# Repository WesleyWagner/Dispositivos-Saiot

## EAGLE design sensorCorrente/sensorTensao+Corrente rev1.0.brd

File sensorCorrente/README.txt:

sensorTensao+Corrente

Para usar o TC:
-Colocar todos os componentes com prefixo "C.*";
-Retirar com prefixo "V.*".

Para usar o sensor de tensão:
-Colocar todos os componentes com prefixo "V.*";
-Retirar com prefixo "C.*".

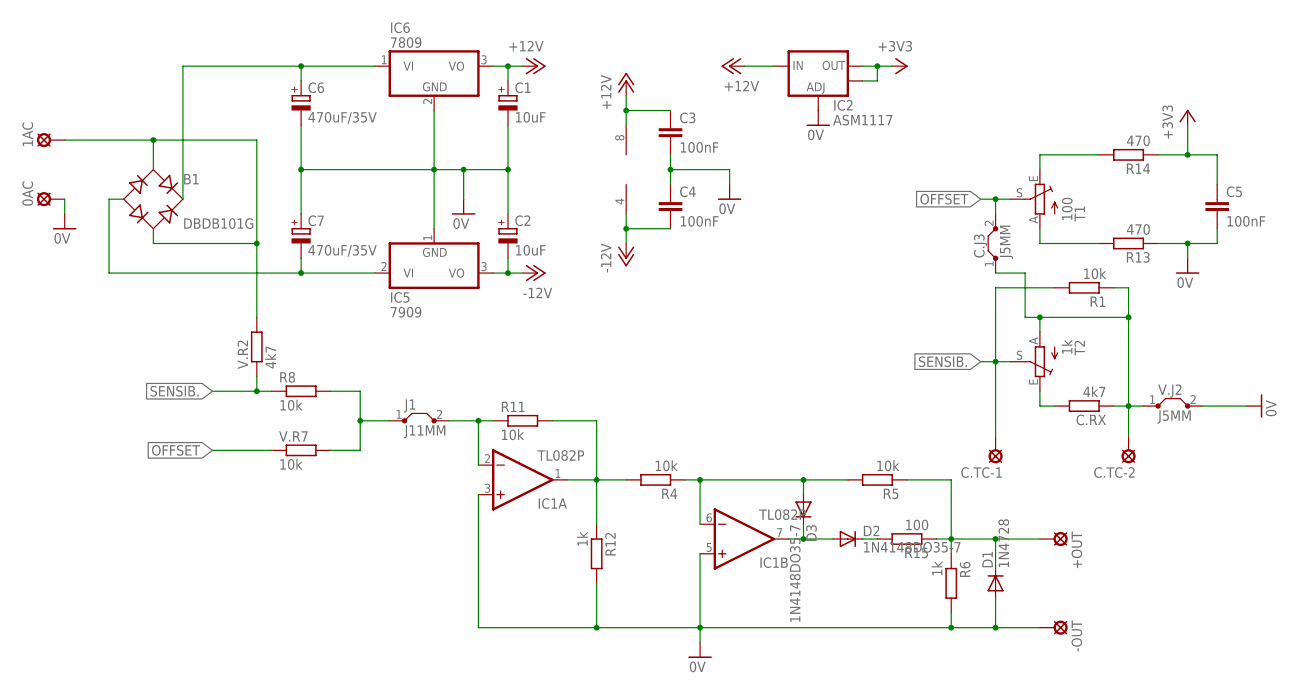
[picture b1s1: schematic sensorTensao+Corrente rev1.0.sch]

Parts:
0AC: 0V; LSP10
1AC: AC; LSP10
+OUT: +D; LSP10
-OUT: 0V; LSP10
B1: DBDB101G; DB
C1, C2: 10uF; E2,5-7
C3, C4, C5: 100nF; C050-024X044
C6, C7: 470uF/35V; E3,5-10
C.J3: J5MM; 05
C.RX: 4k7; 0204/7
C.TC-1, C.TC-2: 0V; LSP10
D1: 1N4728; DO35-7
D2, D3: 1N4148DO35-7; DO35-7
IC1: TL082P; DIL08
IC2: ASM1117; SOT223
IC5: 7909; TO220V
IC6: 7809; TO220V
J1: J11MM; 11
R1, R4, R8, R11: 10k; 0204/7
R5: 10k; 0204/10
R6, R12: 1k; 0204/7
R13, R14: 470; 0204/7
R15: 100; 0204/7
T1: 100; CA6V
T2: 1k; CA6V
V.J2: J5MM; 05
V.R2: 4k7; 0204/7
V.R7: 10k; 0204/7

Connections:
0V: 0AC.MP, -OUT.MP, C1.-, C2.+, C3.2, C4.1, C5.2, C6.-, C7.+, D1.A, IC1.3 (+IN), IC1.5 (+IN), IC2.1 (ADJ), IC5.1 (GND), IC6.2 (GND), R6.2, R12.2, R13.1, V.J2.2
+3V3: C5.1, IC2.2 (OUT), IC2.4 (OUT), R14.1
+12V: C1.+, C3.1, IC1.8 (V+), IC2.3 (IN), IC6.3 (VO)
-12V: C2.-, C4.2, IC1.4 (V-), IC5.3 (VO)
unnamed: B1.+, C6.+, IC6.1 (VI)
unnamed: 1AC.MP, B1.AC1, B1.AC2, V.R2.2
unnamed: C.RX.2, T2.E
unnamed: C.J3.1, C.RX.1, C.TC-2.MP, R1.1, T2.A, V.J2.1
unnamed: IC1.2 (-IN), J1.2, R11.1
unnamed: B1.-, C7.-, IC5.2 (VI)
unnamed: J1.1, R8.2, V.R7.2
unnamed: R14.2, T1.E
unnamed: IC1.1 (OUT), R4.2, R11.2, R12.1
unnamed: D3.A, IC1.6 (-IN), R4.1, R5.2
unnamed: +OUT.MP, D1.C, R5.1, R6.1, R15.1
unnamed: R13.2, T1.A
unnamed: D2.A, D3.C, IC1.7 (OUT)
unnamed: D2.C, R15.2
OFFSET: C.J3.2, T1.S, V.R7.1
SENSIB.: C.TC-1.MP, R1.2, R8.1, T2.S, V.R2.1

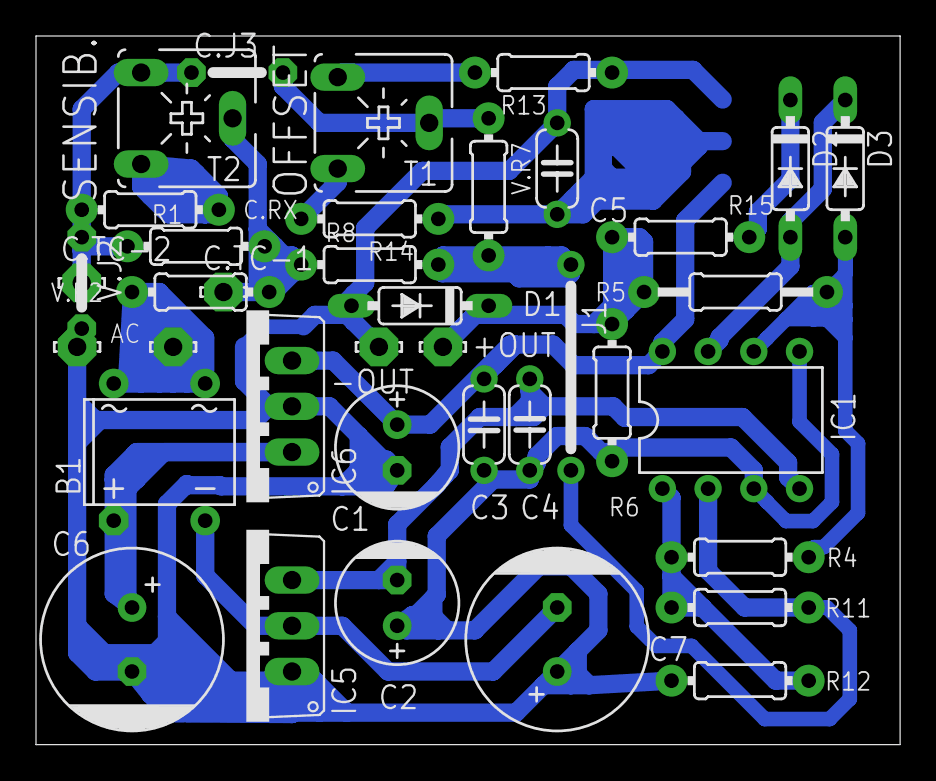
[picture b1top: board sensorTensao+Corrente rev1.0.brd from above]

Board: 2 copper layers, 48.0 x 39.4 mm, 39 parts (1 on the bottom side), 20 nets.

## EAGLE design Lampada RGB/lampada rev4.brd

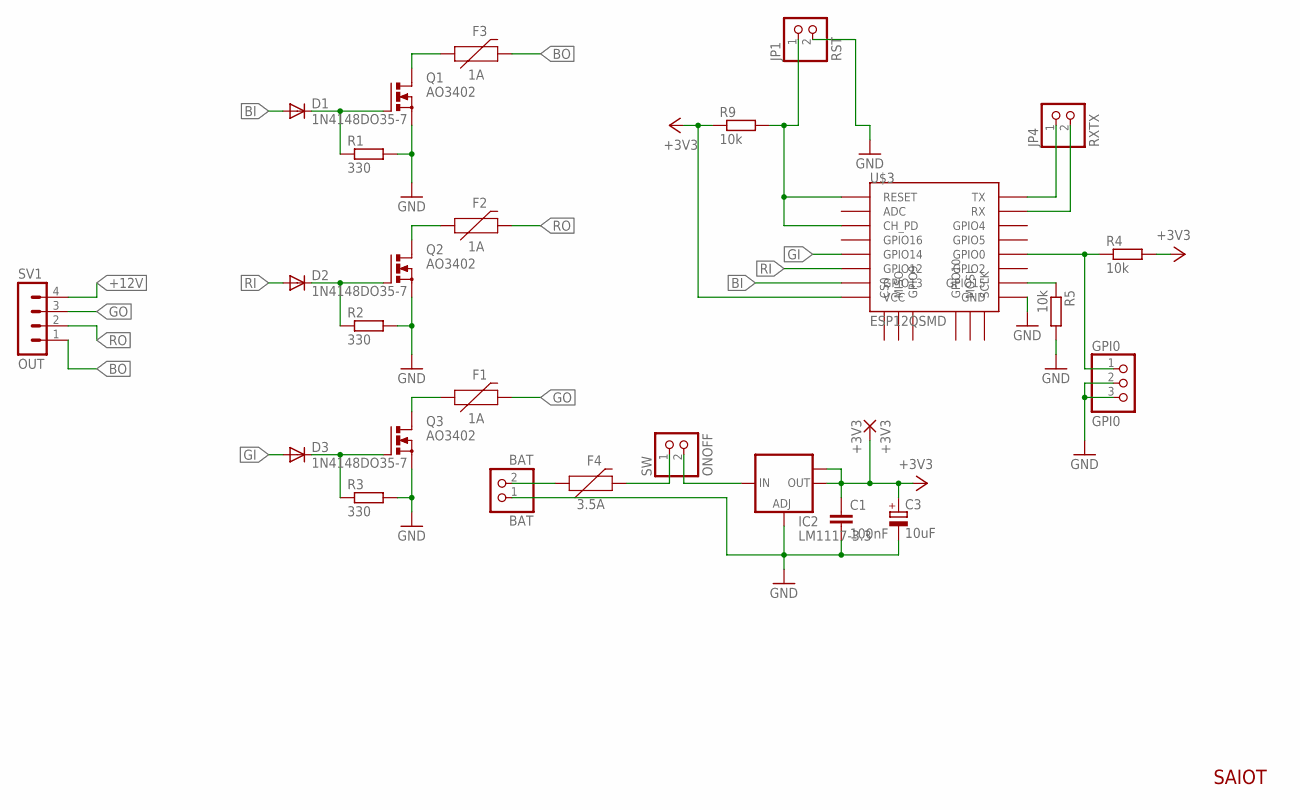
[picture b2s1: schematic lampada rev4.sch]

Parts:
+3V3: +3V3; 2,15/1,0
BAT: BAT; 1X02
C1: 100nF; C050-024X044
C3: 10uF; E2,5-7
D1, D2, D3: 1N4148DO35-7; DO35-7
F1, F2, F3: 1A; 0805
F4: 3.5A; 0805
GPI0: GPI0; 1X03
IC2: LM1117-3.3; SOT223
JP1: RST; 1X02
JP4: RXTX; 1X02
Q1, Q2, Q3: AO3402; SOT-23
R1, R2, R3: 330; 0204/7
R4, R5, R9: 10k; 0204/7
SV1: OUT; MA04-1
SW: ONOFF; 1X02
U$3: ESP12QSMD

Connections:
+3V3: +3V3.1, C1.1, C3.+, IC2.2 (OUT), IC2.TAB (OUT1), R4.2, R9.1, U$3.VCC
+12V: IC2.3 (IN), SV1.4, SW.2
BB: D1.C, Q1.P1 (G), R1.1
BG: D3.C, Q3.P1 (G), R3.1
BI: D1.A, U$3.GPIO13
BO: F3.2, SV1.1
BOFUSE: F3.1, Q1.P3 (D)
BR: D2.C, Q2.P1 (G), R2.1
GI: D3.A, U$3.GPIO14
GND: BAT.1, C1.2, C3.-, GPI0.2, GPI0.3, IC2.1 (ADJ), JP1.2, Q1.P2 (S), Q2.P2 (S), Q3.P2 (S), R1.2, R2.2, R3.2, R5.2, U$3.GND
GO: F1.2, SV1.3
GOFUSE: F1.1, Q3.P3 (D)
GPIO15: R5.1, U$3.GPIO15
unnamed: F4.2, SW.1
unnamed: BAT.2, F4.1
unnamed: JP1.1, R9.2, U$3.CH_PD, U$3.RESET
unnamed: GPI0.1, R4.1, U$3.GPIO0
unnamed: JP4.1, U$3.TX
unnamed: JP4.2, U$3.RX
RI: D2.A, U$3.GPIO12
RO: F2.2, SV1.2
ROFUSE: F2.1, Q2.P3 (D)

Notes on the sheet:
SAIOT

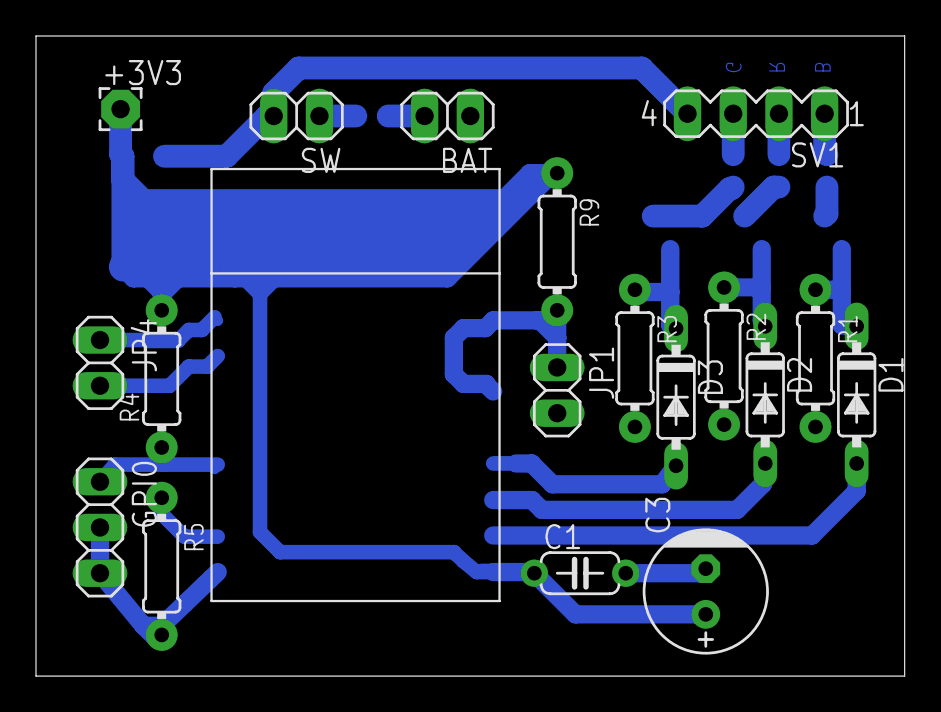
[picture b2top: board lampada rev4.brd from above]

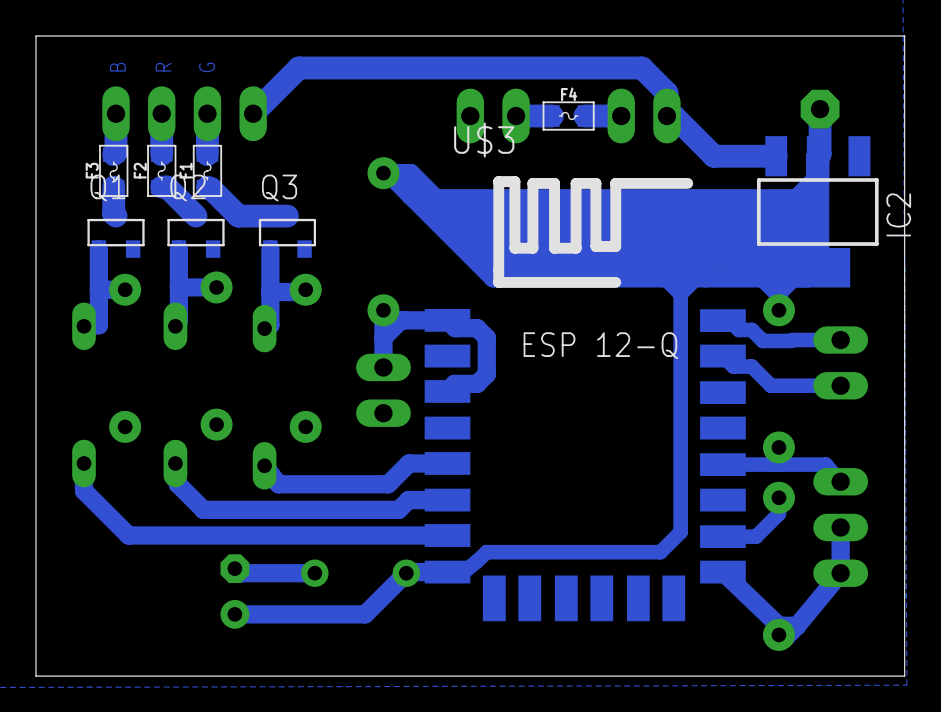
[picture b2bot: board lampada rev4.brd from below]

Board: 2 copper layers, 48.3 x 35.6 mm, 27 parts (9 on the bottom side), 22 nets.

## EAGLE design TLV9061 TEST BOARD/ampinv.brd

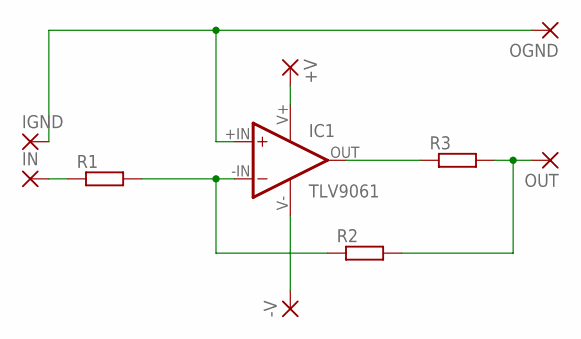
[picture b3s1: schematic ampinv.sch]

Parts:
+V: SMD2; SMD1,27-2,54
-V: SMD2; SMD1,27-2,54
IC1: TLV9061
IGND: SMD2; SMD1,27-2,54
IN: SMD2; SMD1,27-2,54
OGND: SMD2; SMD1,27-2,54
OUT: SMD2; SMD1,27-2,54
R1, R2, R3: R-EU_R0402; R0402

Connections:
GND: IC1.+IN, IGND.1, OGND.1
unnamed: IC1.-IN, R1.2, R2.1
unnamed: IC1.OUT, R3.1
unnamed: OUT.1, R2.2, R3.2
unnamed: -V.1, IC1.V-
unnamed: +V.1, IC1.V+
unnamed: IN.1, R1.1

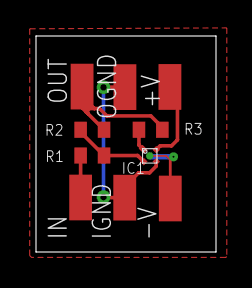
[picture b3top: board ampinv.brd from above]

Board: 2 copper layers, 10.0 x 12.0 mm, 10 parts (0 on the bottom side), 7 nets.

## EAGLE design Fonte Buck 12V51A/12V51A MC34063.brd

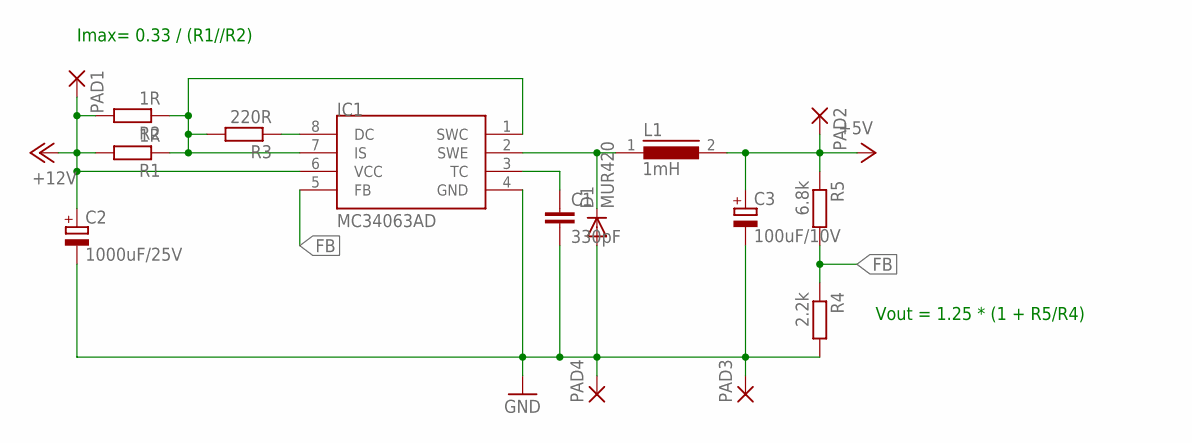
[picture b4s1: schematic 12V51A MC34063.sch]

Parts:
C1: 330pF; C050-024X044
C2: 1000uF/25V; E2,5-7
C3: 100uF/10V; E2,5-7
D1: MUR420; DO35-7
IC1: MC34063AD; SOIC8
L1: 1mH; 82114R
PAD1, PAD2, PAD3, PAD4: 2,54/1,0
R1, R2: 1R; 0204/7
R3: 220R; 0204/7
R4: 2.2k; 0204/7
R5: 6.8k; 0204/7

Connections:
+5V: C3.+, L1.2, PAD2.1, R5.1
+12V: C2.+, IC1.6 (VCC), PAD1.1, R1.2, R2.2
FB: IC1.5 (FB), R4.1, R5.2
GND: C1.2, C2.-, C3.-, D1.A, IC1.4 (GND), PAD3.1, PAD4.1, R4.2
unnamed: IC1.1 (SWC), IC1.7 (IS), R1.1, R2.1, R3.2
unnamed: D1.C, IC1.2 (SWE), L1.1
unnamed: IC1.8 (DC), R3.1
unnamed: C1.1, IC1.3 (TC)

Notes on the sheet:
Imax= 0.33 / (R1//R2)
Vout = 1.25 * (1 + R5/R4)

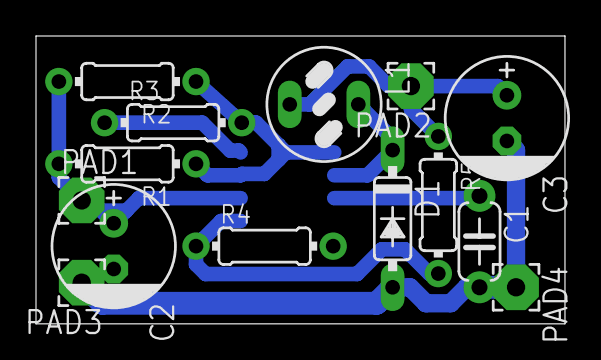
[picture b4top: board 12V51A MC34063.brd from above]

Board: 2 copper layers, 29.4 x 16.0 mm, 15 parts (1 on the bottom side), 8 nets.

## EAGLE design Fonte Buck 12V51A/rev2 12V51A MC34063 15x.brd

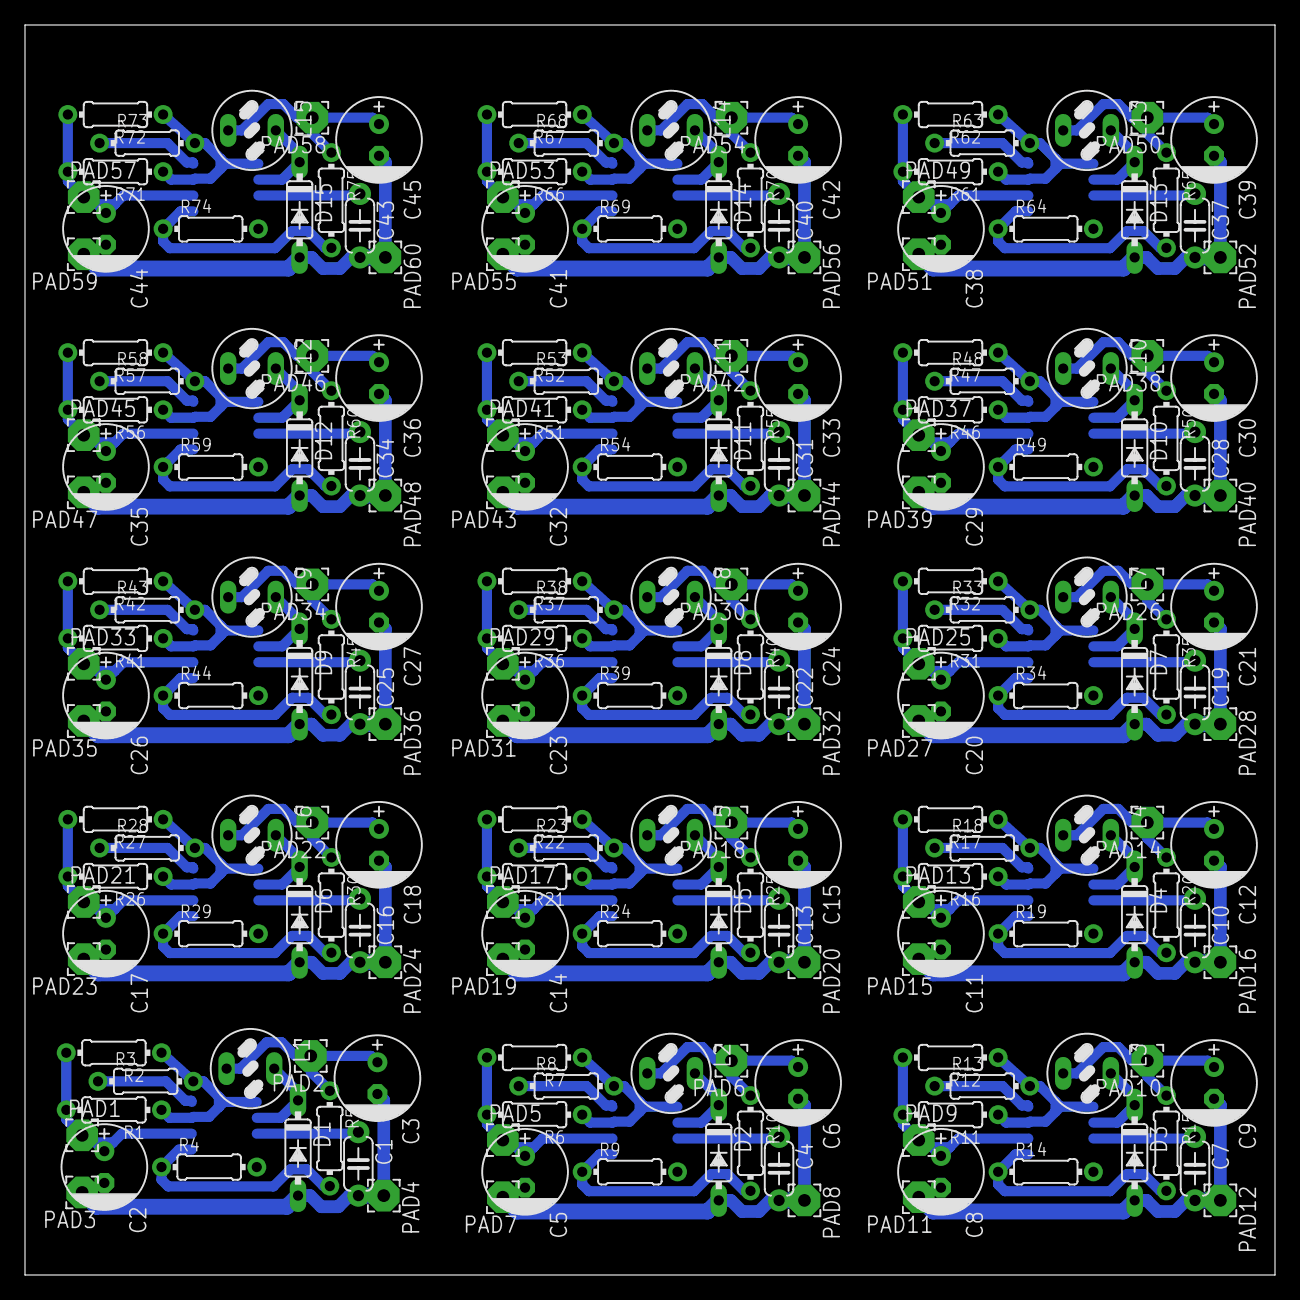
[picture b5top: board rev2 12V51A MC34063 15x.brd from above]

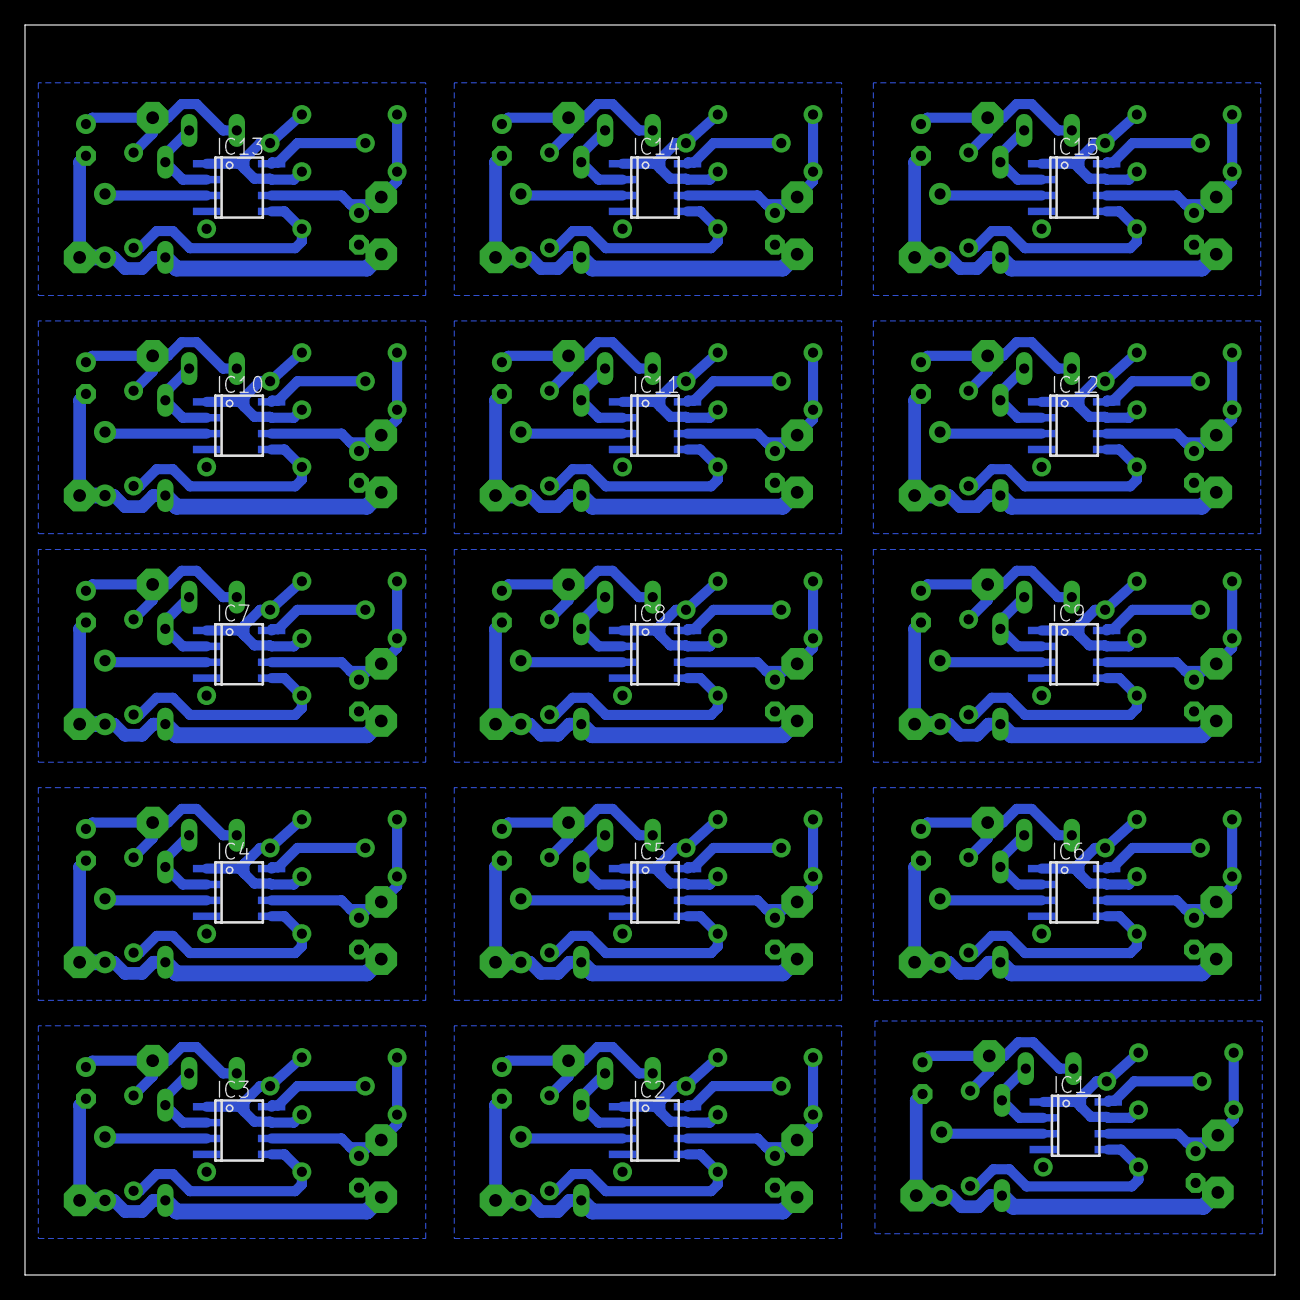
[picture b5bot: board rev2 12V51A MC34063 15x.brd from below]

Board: 2 copper layers, 100.0 x 100.0 mm, 225 parts (15 on the bottom side), 120 nets.

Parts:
C1, C4, C7, C10, C13, C16, C19, C22, C25, C28, C31, C34, C37, C40, C43: 330pF; C050-024X044
C2, C5, C8, C11, C14, C17, C20, C23, C26, C29, C32, C35, C38, C41, C44: 1000uF/25V; E2,5-7
C3, C6, C9, C12, C15, C18, C21, C24, C27, C30, C33, C36, C39, C42, C45: 100uF/10V; E2,5-7
D1, D2, D3, D4, D5, D6, D7, D8, D9, D10, D11, D12, D13, D14, D15: MUR420; DO35-7
IC1, IC2, IC3, IC4, IC5, IC6, IC7, IC8, IC9, IC10, IC11, IC12, IC13, IC14, IC15: MC34063AD; SOIC8
L1, L2, L3, L4, L5, L6, L7, L8, L9, L10, L11, L12, L13, L14, L15: 1mH; 82114R
PAD1, PAD2, PAD3, PAD4, PAD5, PAD6, PAD7, PAD8, PAD9, PAD10, PAD11, PAD12, PAD13, PAD14, PAD15, PAD16, PAD17, PAD18, PAD19, PAD20, PAD21, PAD22, PAD23, PAD24, PAD25, PAD26, PAD27, PAD28, PAD29, PAD30, PAD31, PAD32, PAD33, PAD34, PAD35, PAD36, PAD37, PAD38, PAD39, PAD40, PAD41, PAD42, PAD43, PAD44, PAD45, PAD46, PAD47, PAD48, PAD49, PAD50, PAD51, PAD52, PAD53, PAD54, PAD55, PAD56, PAD57, PAD58, PAD59, PAD60: 2,54/1,0
R1, R2, R6, R7, R11, R12, R16, R17, R21, R22, R26, R27, R31, R32, R36, R37, R41, R42, R46, R47, R51, R52, R56, R57, R61, R62, R66, R67, R71, R72: 1R; 0204/7
R3, R8, R13, R18, R23, R28, R33, R38, R43, R48, R53, R58, R63, R68, R73: 220R; 0204/7
R4, R9, R14, R19, R24, R29, R34, R39, R44, R49, R54, R59, R64, R69, R74: 2.2k; 0204/7
R5, R10, R15, R20, R25, R30, R35, R40, R45, R50, R55, R60, R65, R70, R75: 6.8k; 0204/7

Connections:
+5V: C3.+, L1.2, PAD2.1, R5.1
+5V1: C6.+, L2.2, PAD6.1, R10.1
+5V2: C9.+, L3.2, PAD10.1, R15.1
+5V3: C12.+, L4.2, PAD14.1, R20.1
+5V4: C15.+, L5.2, PAD18.1, R25.1
+5V5: C18.+, L6.2, PAD22.1, R30.1
+5V6: C21.+, L7.2, PAD26.1, R35.1
+5V7: C24.+, L8.2, PAD30.1, R40.1
+5V8: C27.+, L9.2, PAD34.1, R45.1
+5V9: C30.+, L10.2, PAD38.1, R50.1
+5V10: C33.+, L11.2, PAD42.1, R55.1
+5V11: C36.+, L12.2, PAD46.1, R60.1
+5V12: C39.+, L13.2, PAD50.1, R65.1
+5V13: C42.+, L14.2, PAD54.1, R70.1
+5V14: C45.+, L15.2, PAD58.1, R75.1
+12V: C2.+, IC1.6, PAD1.1, R1.2, R2.2
+12V1: C5.+, IC2.6, PAD5.1, R6.2, R7.2
+12V2: C8.+, IC3.6, PAD9.1, R11.2, R12.2
+12V3: C11.+, IC4.6, PAD13.1, R16.2, R17.2
+12V4: C14.+, IC5.6, PAD17.1, R21.2, R22.2
+12V5: C17.+, IC6.6, PAD21.1, R26.2, R27.2
+12V6: C20.+, IC7.6, PAD25.1, R31.2, R32.2
+12V7: C23.+, IC8.6, PAD29.1, R36.2, R37.2
+12V8: C26.+, IC9.6, PAD33.1, R41.2, R42.2
+12V9: C29.+, IC10.6, PAD37.1, R46.2, R47.2
+12V10: C32.+, IC11.6, PAD41.1, R51.2, R52.2
+12V11: C35.+, IC12.6, PAD45.1, R56.2, R57.2
+12V12: C38.+, IC13.6, PAD49.1, R61.2, R62.2
+12V13: C41.+, IC14.6, PAD53.1, R66.2, R67.2
+12V14: C44.+, IC15.6, PAD57.1, R71.2, R72.2
FB: IC1.5, R4.1, R5.2
FB1: IC2.5, R9.1, R10.2
FB2: IC3.5, R14.1, R15.2
FB3: IC4.5, R19.1, R20.2
FB4: IC5.5, R24.1, R25.2
FB5: IC6.5, R29.1, R30.2
FB6: IC7.5, R34.1, R35.2
FB7: IC8.5, R39.1, R40.2
FB8: IC9.5, R44.1, R45.2
FB9: IC10.5, R49.1, R50.2
FB10: IC11.5, R54.1, R55.2
FB11: IC12.5, R59.1, R60.2
FB12: IC13.5, R64.1, R65.2
FB13: IC14.5, R69.1, R70.2
FB14: IC15.5, R74.1, R75.2
GND: C1.2, C2.-, C3.-, D1.A, IC1.4, PAD3.1, PAD4.1, R4.2
GND1: C4.2, C5.-, C6.-, D2.A, IC2.4, PAD7.1, PAD8.1, R9.2
GND2: C7.2, C8.-, C9.-, D3.A, IC3.4, PAD11.1, PAD12.1, R14.2
GND3: C10.2, C11.-, C12.-, D4.A, IC4.4, PAD15.1, PAD16.1, R19.2
GND4: C13.2, C14.-, C15.-, D5.A, IC5.4, PAD19.1, PAD20.1, R24.2
GND5: C16.2, C17.-, C18.-, D6.A, IC6.4, PAD23.1, PAD24.1, R29.2
GND6: C19.2, C20.-, C21.-, D7.A, IC7.4, PAD27.1, PAD28.1, R34.2
GND7: C22.2, C23.-, C24.-, D8.A, IC8.4, PAD31.1, PAD32.1, R39.2
GND8: C25.2, C26.-, C27.-, D9.A, IC9.4, PAD35.1, PAD36.1, R44.2
GND9: C28.2, C29.-, C30.-, D10.A, IC10.4, PAD39.1, PAD40.1, R49.2
GND10: C31.2, C32.-, C33.-, D11.A, IC11.4, PAD43.1, PAD44.1, R54.2
GND11: C34.2, C35.-, C36.-, D12.A, IC12.4, PAD47.1, PAD48.1, R59.2
GND12: C37.2, C38.-, C39.-, D13.A, IC13.4, PAD51.1, PAD52.1, R64.2
GND13: C40.2, C41.-, C42.-, D14.A, IC14.4, PAD55.1, PAD56.1, R69.2
GND14: C43.2, C44.-, C45.-, D15.A, IC15.4, PAD59.1, PAD60.1, R74.2
unnamed: IC1.1, IC1.7, R1.1, R2.1, R3.2
unnamed: IC2.1, IC2.7, R6.1, R7.1, R8.2
unnamed: D1.C, IC1.2, L1.1
unnamed: IC1.8, R3.1
unnamed: IC2.8, R8.1
unnamed: C4.1, IC2.3
unnamed: C1.1, IC1.3
unnamed: D2.C, IC2.2, L2.1
unnamed: IC3.1, IC3.7, R11.1, R12.1, R13.2
unnamed: IC3.8, R13.1
unnamed: C7.1, IC3.3
unnamed: D3.C, IC3.2, L3.1
unnamed: IC4.1, IC4.7, R16.1, R17.1, R18.2
unnamed: IC4.8, R18.1
unnamed: C10.1, IC4.3
unnamed: D4.C, IC4.2, L4.1
unnamed: IC5.1, IC5.7, R21.1, R22.1, R23.2
unnamed: IC5.8, R23.1
unnamed: C13.1, IC5.3
unnamed: D5.C, IC5.2, L5.1
unnamed: IC6.1, IC6.7, R26.1, R27.1, R28.2
unnamed: IC6.8, R28.1
unnamed: C16.1, IC6.3
unnamed: D6.C, IC6.2, L6.1
unnamed: IC7.1, IC7.7, R31.1, R32.1, R33.2
unnamed: IC7.8, R33.1
unnamed: C19.1, IC7.3
unnamed: D7.C, IC7.2, L7.1
unnamed: IC8.1, IC8.7, R36.1, R37.1, R38.2
unnamed: IC8.8, R38.1
unnamed: C22.1, IC8.3
unnamed: D8.C, IC8.2, L8.1
unnamed: IC9.1, IC9.7, R41.1, R42.1, R43.2
unnamed: IC9.8, R43.1
unnamed: C25.1, IC9.3
unnamed: D9.C, IC9.2, L9.1
unnamed: IC10.1, IC10.7, R46.1, R47.1, R48.2
unnamed: IC10.8, R48.1
unnamed: C28.1, IC10.3
unnamed: D10.C, IC10.2, L10.1
unnamed: IC11.1, IC11.7, R51.1, R52.1, R53.2
unnamed: IC11.8, R53.1
unnamed: C31.1, IC11.3
unnamed: D11.C, IC11.2, L11.1
unnamed: IC12.1, IC12.7, R56.1, R57.1, R58.2
unnamed: IC12.8, R58.1
unnamed: C34.1, IC12.3
unnamed: D12.C, IC12.2, L12.1
unnamed: IC13.1, IC13.7, R61.1, R62.1, R63.2
unnamed: IC13.8, R63.1
unnamed: C37.1, IC13.3
unnamed: D13.C, IC13.2, L13.1
unnamed: IC14.1, IC14.7, R66.1, R67.1, R68.2
unnamed: IC14.8, R68.1
unnamed: C40.1, IC14.3
unnamed: D14.C, IC14.2, L14.1
unnamed: IC15.1, IC15.7, R71.1, R72.1, R73.2
unnamed: IC15.8, R73.1
unnamed: C43.1, IC15.3
unnamed: D15.C, IC15.2, L15.1

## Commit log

2019-03-16 Add files via upload
    Testando armazenamento de dados de estado na flash
2019-03-16 AgoraVai
2019-03-24 Dispositivos
    Inclusão do sensor de tensão e o conversor DC-DC utilizando o MC34063.
2019-03-26 Fusíveis
    Adição de fusíveis na Tira de Led e na lampada RGB
2019-03-30 Sensor de corrente usando TC
    Adição do sensor de corrente usando um TC com a proteção do sensor de tensão
2019-05-03 Sensor de Tensão
    Código do Sensor de Tensão
2019-05-03 Revert "Sensor de Tensão"
    This reverts commit dab632c7a57fa9342688e34f637e3df35825bc6e.
2019-05-03 VoltageDevice
    Código do Sensor de Tensão

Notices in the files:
parts and their libraries:
SparkFun-Fuses: Licensing: Creative Commons ShareAlike 4.0 International - https://creativecommons.org/licenses/by-sa/4.0
